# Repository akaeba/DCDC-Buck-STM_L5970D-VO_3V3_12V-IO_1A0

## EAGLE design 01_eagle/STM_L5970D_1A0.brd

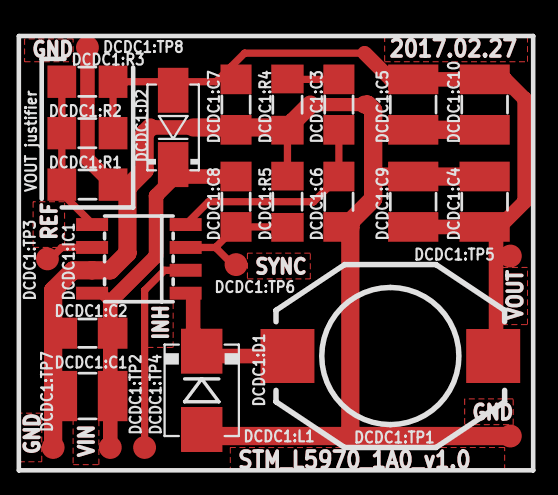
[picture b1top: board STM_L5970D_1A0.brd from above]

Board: 2 copper layers, 27 parts (0 on the bottom side), 10 nets.

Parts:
DCDC1:C1: 10µ/35V; 1210
DCDC1:C2, DCDC1:C7: 100n/50V; 1206
DCDC1:C3: 22n/50V; 1206
DCDC1:C4, DCDC1:C5, DCDC1:C9, DCDC1:C10: 47µ/16V; 1210
DCDC1:C6: 220p/50V; 1206
DCDC1:C8: 1µ/50V; 1206
DCDC1:D1: MBRS240; DO214AA
DCDC1:D2: RS1B; DO214AC
DCDC1:IC1: L5970D; SOIC08
DCDC1:L1: 33µ; PISM
DCDC1:R1: 3K3; 1206
DCDC1:R2: 11K; 1206
DCDC1:R3: 120K; 1206
DCDC1:R4: 4K7; 1206
DCDC1:R5: 47K; 1206
DCDC1:TP1, DCDC1:TP2, DCDC1:TP3, DCDC1:TP4, DCDC1:TP5, DCDC1:TP6, DCDC1:TP7, DCDC1:TP8: TPB1,27; B1,27

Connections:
DCDC1:GND: DCDC1:C1.2, DCDC1:C2.2, DCDC1:C4.2, DCDC1:C5.2, DCDC1:C6.2, DCDC1:C7.2, DCDC1:C9.2, DCDC1:C10.2, DCDC1:D1.A, DCDC1:IC1.7, DCDC1:R1.1, DCDC1:R4.1, DCDC1:R5.1, DCDC1:TP1.TP, DCDC1:TP7.TP, DCDC1:TP8.TP
DCDC1:INH: DCDC1:C8.2, DCDC1:IC1.3, DCDC1:R5.2, DCDC1:TP6.TP
DCDC1:N$1: DCDC1:D1.C, DCDC1:IC1.1, DCDC1:L1.1
DCDC1:N$2: DCDC1:IC1.5, DCDC1:R1.2, DCDC1:R2.1, DCDC1:R3.1
DCDC1:N$3: DCDC1:C3.1, DCDC1:C6.1, DCDC1:IC1.4
DCDC1:N$4: DCDC1:C3.2, DCDC1:R4.2
DCDC1:SYNC: DCDC1:IC1.2, DCDC1:TP4.TP
DCDC1:VIN: DCDC1:C1.1, DCDC1:C2.1, DCDC1:C8.1, DCDC1:D2.C, DCDC1:IC1.8, DCDC1:TP2.TP
DCDC1:VOUT: DCDC1:C4.1, DCDC1:C5.1, DCDC1:C7.1, DCDC1:C9.1, DCDC1:C10.1, DCDC1:D2.A, DCDC1:L1.2, DCDC1:R2.2, DCDC1:R3.2, DCDC1:TP5.TP
DCDC1:VREF: DCDC1:IC1.6, DCDC1:TP3.TP

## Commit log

2018-02-18 Github Release from internal Repo -> SHA-1: cd59704e4ff1f6669844b176fe542517aaf3a12c

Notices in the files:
parts and their libraries:
omcCapacitor: Copyright & License
This library is licensed under the General Public License, Version 2.
More Information about the General Public License is available at http://www.gnu.org/copyleft/gpl.html.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
omcDiode: This library is licensed under the General Public License, Version 3.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
